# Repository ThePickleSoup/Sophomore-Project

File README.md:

# Sophomore-Project
Repository for Sophomore Project Lab course
licensed under the GNU General Public License v3.0

The following documents are an assortment of files found or created for my Sophomore Project course.
We are working on designing a PV-Battery Integrated Energy Source.
My role is the group is Designer. My tasks are to create the code and CAD deisgns for the project.
> blah blah blah, insert something about what that is. look it up idk.

The current Arduino code that is being employed is titled: Project_Main

Tasks for code
--------------
 - My Tasks for code have been shelved

Tasks for PCB design
--------------
 - Decide what PCB deisgn software to use  
  Done. Using KiCad
  
 - Design it(?)                            
  Done. Prototype design was completed and presented. Was not milled.

Tasks for CAD Design
--------------
 - Learn Solidworks                        
  Done. I can model well enough

 - Design an enclosure or a stand     
  Incomplete

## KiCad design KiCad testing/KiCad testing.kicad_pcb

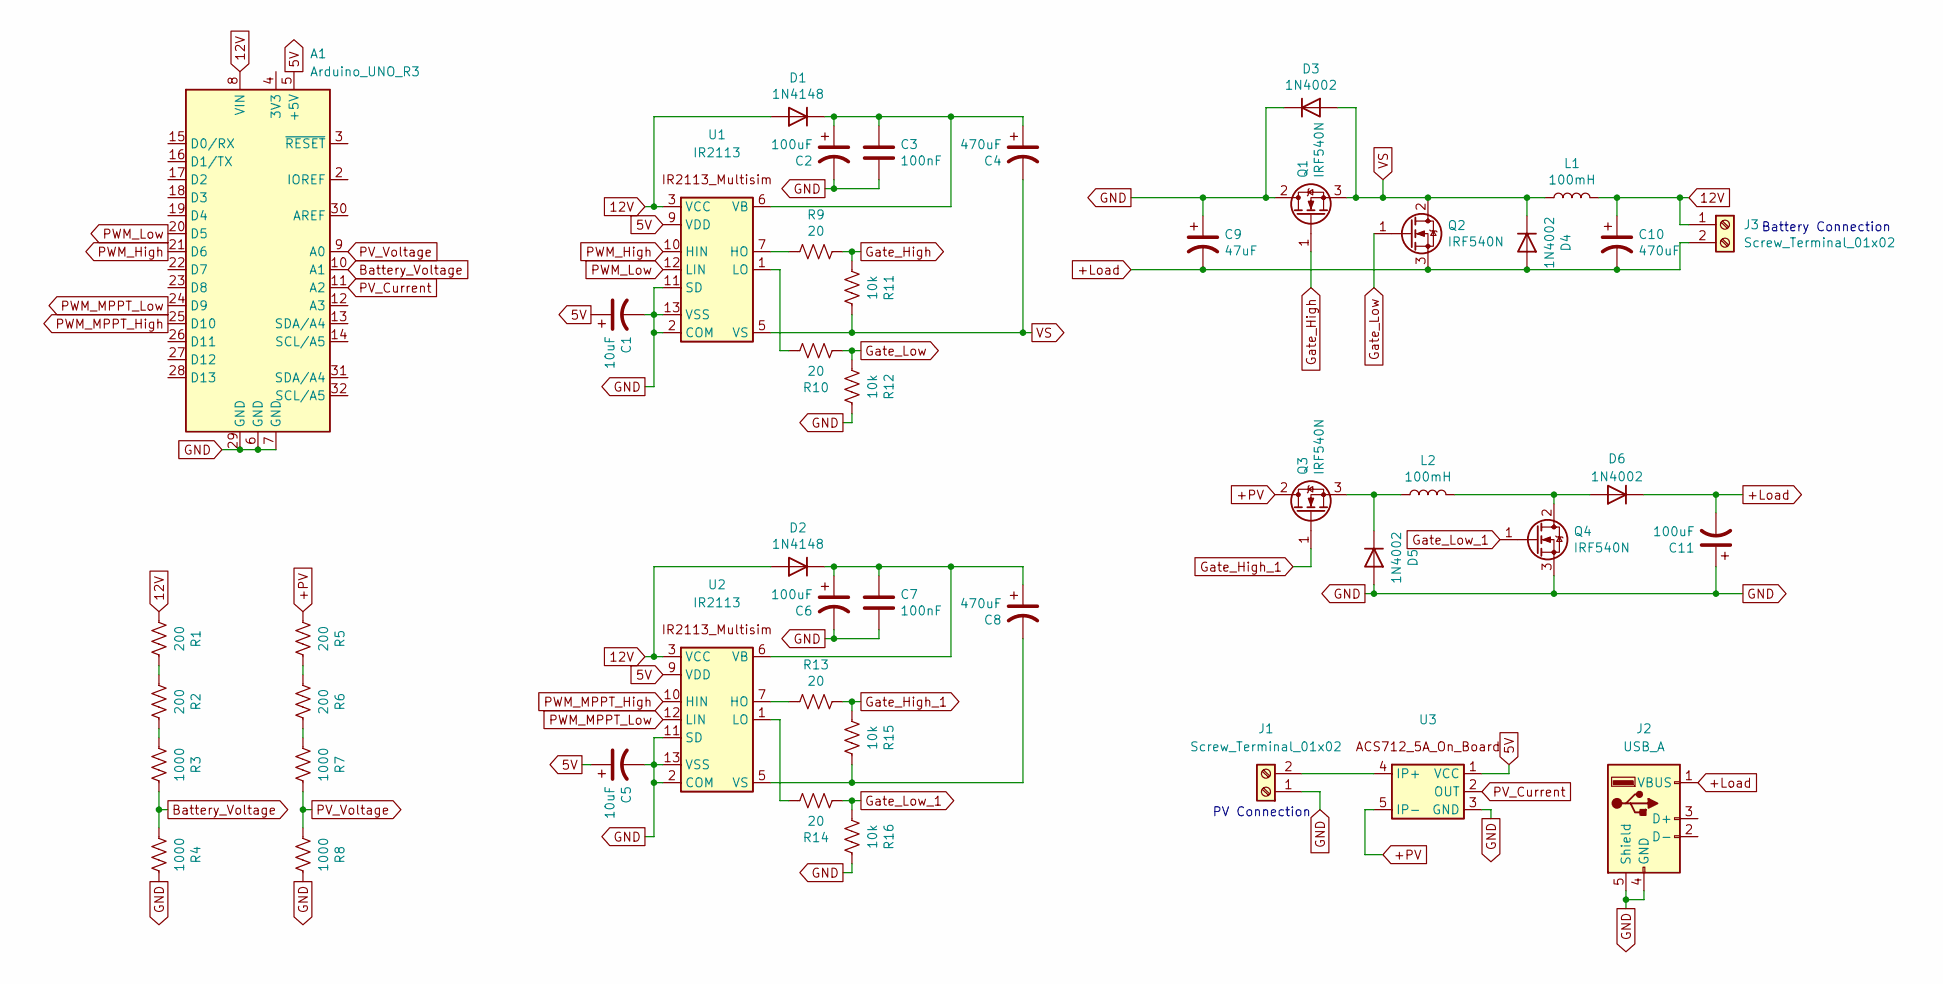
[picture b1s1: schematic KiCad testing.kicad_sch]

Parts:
A1: Arduino_UNO_R3
C1, C5: 10uF; CP_Radial_D5.0mm_P2.00mm
C2, C6: 100uF; CP_Radial_D5.0mm_P2.00mm
C3, C7: 100nF; C_Disc_D4.7mm_W2.5mm_P5.00mm
C4, C8, C10: 470uF; CP_Radial_D10.0mm_P5.00mm
C9: 47uF; CP_Radial_D6.3mm_P2.50mm
C11: 100uF; CP_Radial_D10.0mm_P5.00mm
D1, D2: 1N4148; D_DO-35_SOD27_P7.62mm_Horizontal
D3, D4, D5, D6: 1N4002; D_DO-41_SOD81_P10.16mm_Horizontal
J1, J3: Screw_Terminal_01x02; TerminalBlock_Altech_AK300-2_P5.00mm
J2: USB_A; USB_A_CONNFLY_DS1095-WNR0
L1, L2: 100mH; L_Radial_D10.5mm_P5.00mm_Abacron_AISR-01
Q1, Q2, Q3, Q4: IRF540N; TO-220-3_Vertical
R1, R2, R5, R6: 200; R_Axial_DIN0207_L6.3mm_D2.5mm_P10.16mm_Horizontal
R3, R4, R7, R8: 1000; R_Axial_DIN0207_L6.3mm_D2.5mm_P10.16mm_Horizontal
R9, R10, R13, R14: 20; R_Axial_DIN0207_L6.3mm_D2.5mm_P10.16mm_Horizontal
R11, R12, R15, R16: 10k; R_Axial_DIN0207_L6.3mm_D2.5mm_P10.16mm_Horizontal
U1, U2: IR2113; DIP-14_W7.62mm
U3: (no value)

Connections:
5V: A1.5 (+5V), C1.1, C5.1, U1.9 (VDD), U2.9 (VDD), U3.1 (VCC)
12V: A1.8 (VIN), C10.1, D1.2 (A), D2.2 (A), J3.1, L1.2, R1.1, U1.3 (VCC), U2.3 (VCC)
+Load: C9.2, C10.2, C11.2, D4.2 (A), D6.1 (K), J2.1 (VBUS), J3.2, Q2.3 (S)
+PV: Q3.2 (D), R5.1, U3.5 (IP-)
Battery_Voltage: A1.10 (A1), R3.2, R4.1
GND: A1.6 (GND), A1.7 (GND), A1.29 (GND), C1.2, C2.2, C3.2, C5.2, C6.2, C7.2, C9.1, C11.1, D3.1 (K), D5.2 (A), J1.1, J2.4 (GND), J2.5 (Shield), Q1.2 (D), Q4.3 (S), R4.2, R8.2, R12.2, R16.2, U1.2 (COM), U1.11 (SD), U1.13 (VSS), U2.2 (COM), U2.11 (SD), U2.13 (VSS), U3.3 (GND)
Gate_High: Q1.1 (G), R9.2, R11.1
Gate_High_1: Q3.1 (G), R13.2, R15.1
Gate_Low: Q2.1 (G), R10.1, R12.1
Gate_Low_1: Q4.1 (G), R14.1, R16.1
unnamed: C2.1, C3.1, C4.1, D1.1 (K), U1.6 (VB)
unnamed: C6.1, C7.1, C8.1, D2.1 (K), U2.6 (VB)
unnamed: D5.1 (K), L2.1, Q3.3 (S)
unnamed: D6.2 (A), L2.2, Q4.2 (D)
unnamed: J1.2, U3.4 (IP+)
unnamed: R1.2, R2.1
unnamed: R2.2, R3.1
unnamed: R5.2, R6.1
unnamed: R6.2, R7.1
unnamed: R9.1, U1.7 (HO)
unnamed: R10.2, U1.1 (LO)
unnamed: R13.1, U2.7 (HO)
unnamed: R14.2, U2.1 (LO)
unnamed: C8.2, R15.2, U2.5 (VS)
PV_Current: A1.11 (A2), U3.2 (OUT)
PV_Voltage: A1.9 (A0), R7.2, R8.1
PWM_High: A1.21 (D6), U1.10 (HIN)
PWM_Low: A1.20 (D5), U1.12 (LIN)
PWM_MPPT_High: A1.25 (D10), U2.10 (HIN)
PWM_MPPT_Low: A1.24 (D9), U2.12 (LIN)
VS: C4.2, D3.2 (A), D4.1 (K), L1.1, Q1.3 (S), Q2.2 (D), R11.2, U1.5 (VS)

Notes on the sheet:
Battery Connection
PV Connection

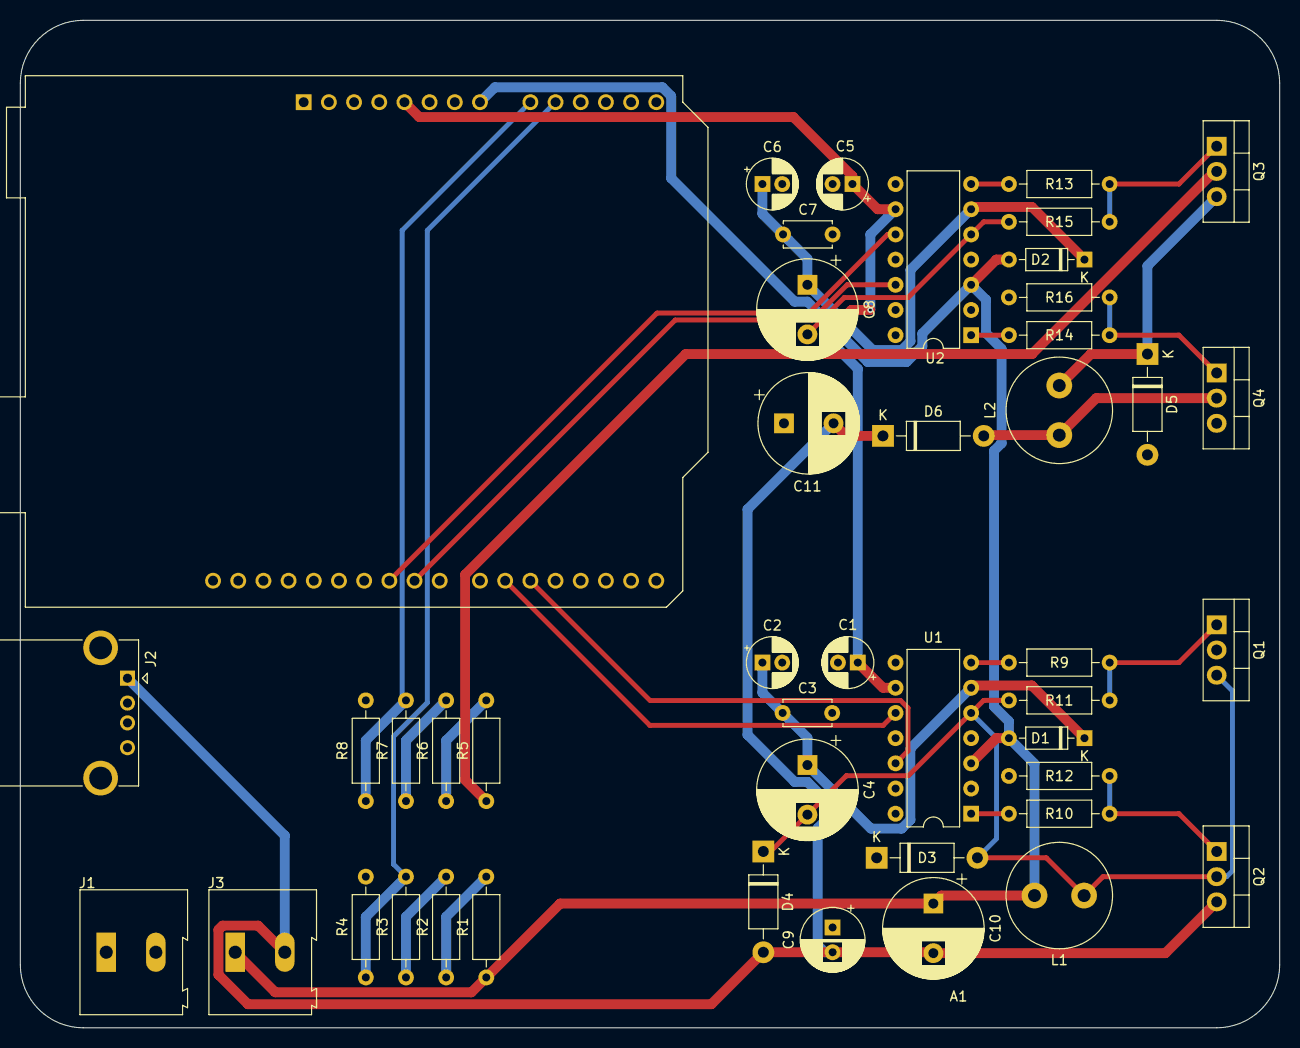
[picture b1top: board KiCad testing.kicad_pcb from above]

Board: 2 copper layers, 127.0 x 101.6 mm, 45 parts (0 on the bottom side), 29 nets.

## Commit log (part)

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2023-09-11 Upload PWM file for MSP432
    Code Composer Studio is required to properly run this code.
2023-09-27 Create MIcrocontrollerTestCode.ino
    Code designed to give an output to the gate driver. Does not do anything but output two basic square wave signals.
2023-10-03 Worked on Arduino Code
    Worked on Arduino code to produce a proper PWM signal from two pins. Moved to a new file named "MTC_V2.ino".
2023-10-09 Edited Code
    Edited code for both MicrocontrollerTestCode and MTC_V2
2023-10-09 Created MTC_V3
    Third attempt to create an alternating PWM signal to control our gate driver. This time I am using timer registers instead of delays.
2023-10-09 Revise MTC_V3.ino
2023-10-09 Remove Unnecessary Files
    Removed files related to the MSP432, as they are not needed for the project.
2023-10-09 Remove Unnecessary Files
    Removed more files related to the MSP432.
2023-10-09 Removed Even MORE Unnecessary files
2023-10-10 Added Example Code folder
    Added Example Code folder, and within MPPT_design_1. Added software version identifiers into the MTC files, software version counting starts as of now.
2023-10-10 Create MTC_V4.ino
    Fourth attempt to create an alternating PWM signal to control our gate driver.
    Update MPPT_openai_1.ino to use the TimerOne.h library instead of directly changing the timer registers.
2023-10-11 Started testing KiCad
    Started working on a KiCad project. Might not actually use it.
2023-10-26 KiCad Schematics
2023-10-27 Updated Schematic
2023-10-27 Update Schematic
2023-11-01 Update Schematic
    Begin PCB layout. Not final design.
2023-11-27 Update schematic and redesign pcb layout.
2023-11-27 Start designing the 3d printed project box.
2023-11-27 update pcb
2023-12-07 Making new schematic/pcb file
2023-12-09 Schematic and PCB Redesign
    Double checked all connections in the schematic.
    1. Changed the Arduino Nano to an Arduino Uno Rev3
    2. Changed the schematic for the two IR2113 nets so that they are more coherent.
    3. Added and fixed certain things with the voltage and current sensors
    4. Cleaned up the global labels.
    Started redesigning the PCB to follow updated schematic and several other constraints.
2023-12-11 Update Schematic
    Here the design for the PCB is more or less in a good spot. The gate drivers may get expanded some to take up more room (to make it easier to tell which components go where in the PCB). Most of the t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
2023-12-11 First PCB Final
    Here the PCB is fully connected. I do not like the design, but it is fully connected either way. The PCB is still missing the current sensor, as I have no way of knowing what components the small boa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
    If I had more time, this design would definitely be reworked.
2023-12-13 Folder Restructure
    Moved some folders around and added some new .pdf and .ino files.
    Project_Main.ino is our currently implemented code.
    Electronic Lab Notebook.pdf has notes from the project manager.
    Removed an unneeded KiCad Project.
2023-12-13 Added Reports
2023-12-16 Created Final Report.pdf
